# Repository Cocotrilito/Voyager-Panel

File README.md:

<div align="center">

# ⟡ VOYAGER PANEL ⟡

### An E-Ink travel dashboard

`ESP32-S3` · `296×128 E-Paper` · `Battery Powered` · `Wi-Fi` · `Low Power`

</div>

---

An E-Ink travel dashboard. with an ESP32-S3 Showing weather, hackclub countdowns, and travel info for hackactons. this dashboard has Low-Power consumption, Wi-Fi connected, battery-operated!!!!

---

## ⟡ The reason behind this project

This project started from the *dream* of always wanting to have a big countdown telling you the Narrow door for a better future is closing, yeah crazy right?, hahaha well actually this project started in the supermarket of my local city, I was shopping and noticed an E-Ink display, I thought *I have seen this before* and it was when I was searching my first project I saw something called E-Ink dashboard, and was cool but I thought Im too newbie for this, so I challenged myself to improve my PCB designer skills and I think I did a really cool project, im really proud of it tbh, well but in the end the actual big reason is to truly have a giant countdown telling you stasis is over in X days or telling you your youth days are over in X days I love presure >:D

---

## ⟡ Schematic Overview

<div align="center">

</div>

---

## ⟡ PCB — DIFFERENT VERSIONS

<div align="center">

</div>

<table>
<tr>
<td width="50%"></td>
<td width="50%"></td>
</tr>
<tr>
<td align="center"><b>Back copper</b></td>
<td align="center"><b>Front copper</b></td>
</tr>
</table>

---

## ⟡ RENDER!!

<div align="center">

</div>

<table>
<tr>
<td width="50%"></td>
<td width="50%"></td>
</tr>
<tr>
<td align="center"><b>Front</b></td>
<td align="center"><b>Back</b></td>
</tr>
</table>

---

## ⟡ Hardware at a glance

| | |
|---|---|
| **MCU** | ESP32-S3-MINI-1 — Wi-Fi, BLE, native USB |
| **Display** | Waveshare 2.9" e-Paper, 296×128, SSD1680 controller |
| **Sensor** | BMP280 over I2C — temperature, pressure, derived altitude |
| **Power** | 1000 mAh LiPo, TP4056 charger, MCP1700 LDO |
| **Protection** | TVS ESD array, Schottky reverse-current diode, 500 mA polyfuse |
| **Programming** | Native USB-C, no external UART bridge |

---

## ⟡ Firmware

Built with **PlatformIO** on the Arduino framework.

```
firmware/VoyagerPanelFirmware/
├── platformio.ini
└── src/
    ├── main.cpp
    └── images.h
```

Because the board uses the ESP32-S3's native USB and carries no USB-UART bridge,
`Serial` has to be routed to the USB CDC peripheral. Without these flags nothing
reaches the host:

```ini
build_flags =
    -D ARDUINO_USB_MODE=1
    -D ARDUINO_USB_CDC_ON_BOOT=1
```

The sensor and the display initialise **independently**, so a failure in one does not
take down the other. The dashboard degrades gracefully instead of hanging.

### Live telemetry

```
========== VOYAGER SENSOR ==========
  Temperature : 29.29 C
  Pressure    : 751.36 hPa
  Altitude    : 2452.2 m
====================================
```

---

## ⟡ Debugging log

The display refused to render, and tracking down why turned into the most interesting
part of this build — a full diagnosis of a hardware fault carried out **without a
multimeter**, using the microcontroller itself as the measuring instrument.

Short version: the SSD1680 was running on **phantom power**, leaking current through
its own ESD protection diodes. Enough to acknowledge a reset, not enough to execute a
single SPI command.

The full write-up, including the software continuity matrix used to prove it, lives in
**[DEBUGGING.md](DEBUGGING.md)**.

A second find along the way: the module sold as a BME280 is actually a **BMP280**. Its
chip ID register returns `0x58` instead of `0x60`, and it has no humidity channel. The
firmware reads that register and picks the right driver rather than trusting the label.

---

## ⟡ BOM

| Name | Purpose | Qty | Cost (USD) | Distributor |
|------|---------|-----|-----------|-------------|
| ESP32-S3-MINI-1 | Main microcontroller with WiFi and USB native | 1 | $8.50 | AliExpress |
| Waveshare 2.9inch e-Paper Module | Main e-ink display 296x128px | 1 | $17.00 | AliExpress |
| BME280 Breakout Module | Temperature/Humidity/Pressure sensor | 1 | $5.15 | AliExpress |
| LiPo Battery 1000mAh 3.7V | Portable power source | 1 | $5.00 | Local Ecuador |
| USB-C Receptacle 16P | Power input and native USB programming | 1 | $0.50 | JLCPCB |
| JST PH 2mm 2-Pin Connector | Battery connector | 1 | $0.10 | JLCPCB |
| Pin Header 1x08 2.54mm | E-ink display connector | 1 | $0.05 | Local |
| Pin Header 1x04 2.54mm | BME280 module connector | 1 | $0.05 | Local |
| TP4056-42-ESOP8 | LiPo battery charger IC | 1 | $0.15 | JLCPCB |
| MCP1700-3302 SOT-89 | 3.3V LDO regulator 0.2V dropout | 1 | $0.45 | JLCPCB |
| SP0503BAHTG SOT-363 | TVS ESD protection diode for USB | 1 | $0.20 | JLCPCB |
| SS14 SMA | Schottky diode reverse current protection | 1 | $0.05 | JLCPCB |
| Polyfuse 500mA 1206 | Resettable overcurrent fuse | 1 | $0.10 | JLCPCB |
| SW_SPST_TL3342 | Tactile buttons Reset/Boot/Next/Select | 4 | $0.05 | JLCPCB |
| LED 0805 Red | Battery charging indicator CHRG | 1 | $0.02 | JLCPCB |
| LED 0805 Blue | Standby indicator STDBY | 1 | $0.02 | JLCPCB |
| LED 0805 Green | System status indicator | 1 | $0.02 | JLCPCB |
| Resistor 1k 0805 | LED current limiting resistors | 3 | $0.03 | JLCPCB |
| Resistor 2.2k 0805 | TP4056 charge current set 550mA | 1 | $0.01 | JLCPCB |
| Resistor 4.7k 0805 | I2C SDA/SCL pull-up resistors | 2 | $0.02 | JLCPCB |
| Resistor 5.1k 0805 | USB-C CC1/CC2 pull-down resistors | 2 | $0.02 | JLCPCB |
| Resistor 10k 0805 | Pull-ups for EN/BOOT/UI buttons | 5 | $0.05 | JLCPCB |
| Resistor 27R 0805 | USB D+/D- series termination | 2 | $0.02 | JLCPCB |
| Capacitor 100nF 0805 | High frequency decoupling | 5 | $0.05 | JLCPCB |
| Capacitor 1uF 0805 | EN pin reset debounce | 1 | $0.02 | JLCPCB |
| Capacitor 10uF 0805 | Bulk decoupling capacitors | 5 | $0.15 | JLCPCB |
| Capacitor 22uF 0805 | ESP32 main power bulk decoupling | 1 | $0.05 | JLCPCB |
| PCB + SMT Assembly | 2-layer PCB with PCBA | 1 | $47.90 | JLCPCB |
| **TOTAL** | | | **$85.42** | |

---

## ⟡ Repository layout

```
├── cad/                          Fusion 360 enclosure + renders
├── docs/references/              Datasheets and reference material
├── firmware/
│   ├── VoyagerPanelFirmware/     PlatformIO project
│   └── diagnostics/              Hardware bring-up test sketches
├── images/                       Schematic, PCB, and build photos
├── projectFiles/
├── voyagerPanel/                 KiCad project
├── DEBUGGING.md
└── README.md
```

---

## ⟡ Final notes!

Thanks for reading! made possible with http://stasis.hackclub.com/

---

<div align="center">

## ⟡ me

*By cocotrilo*

**made with luv (THIS ONE was with a lot of love, EXCEPT FOR THE BOM PLEASE DONT USE EVER ALIEXPRESS) Nk but luv from EC <3**

</div>

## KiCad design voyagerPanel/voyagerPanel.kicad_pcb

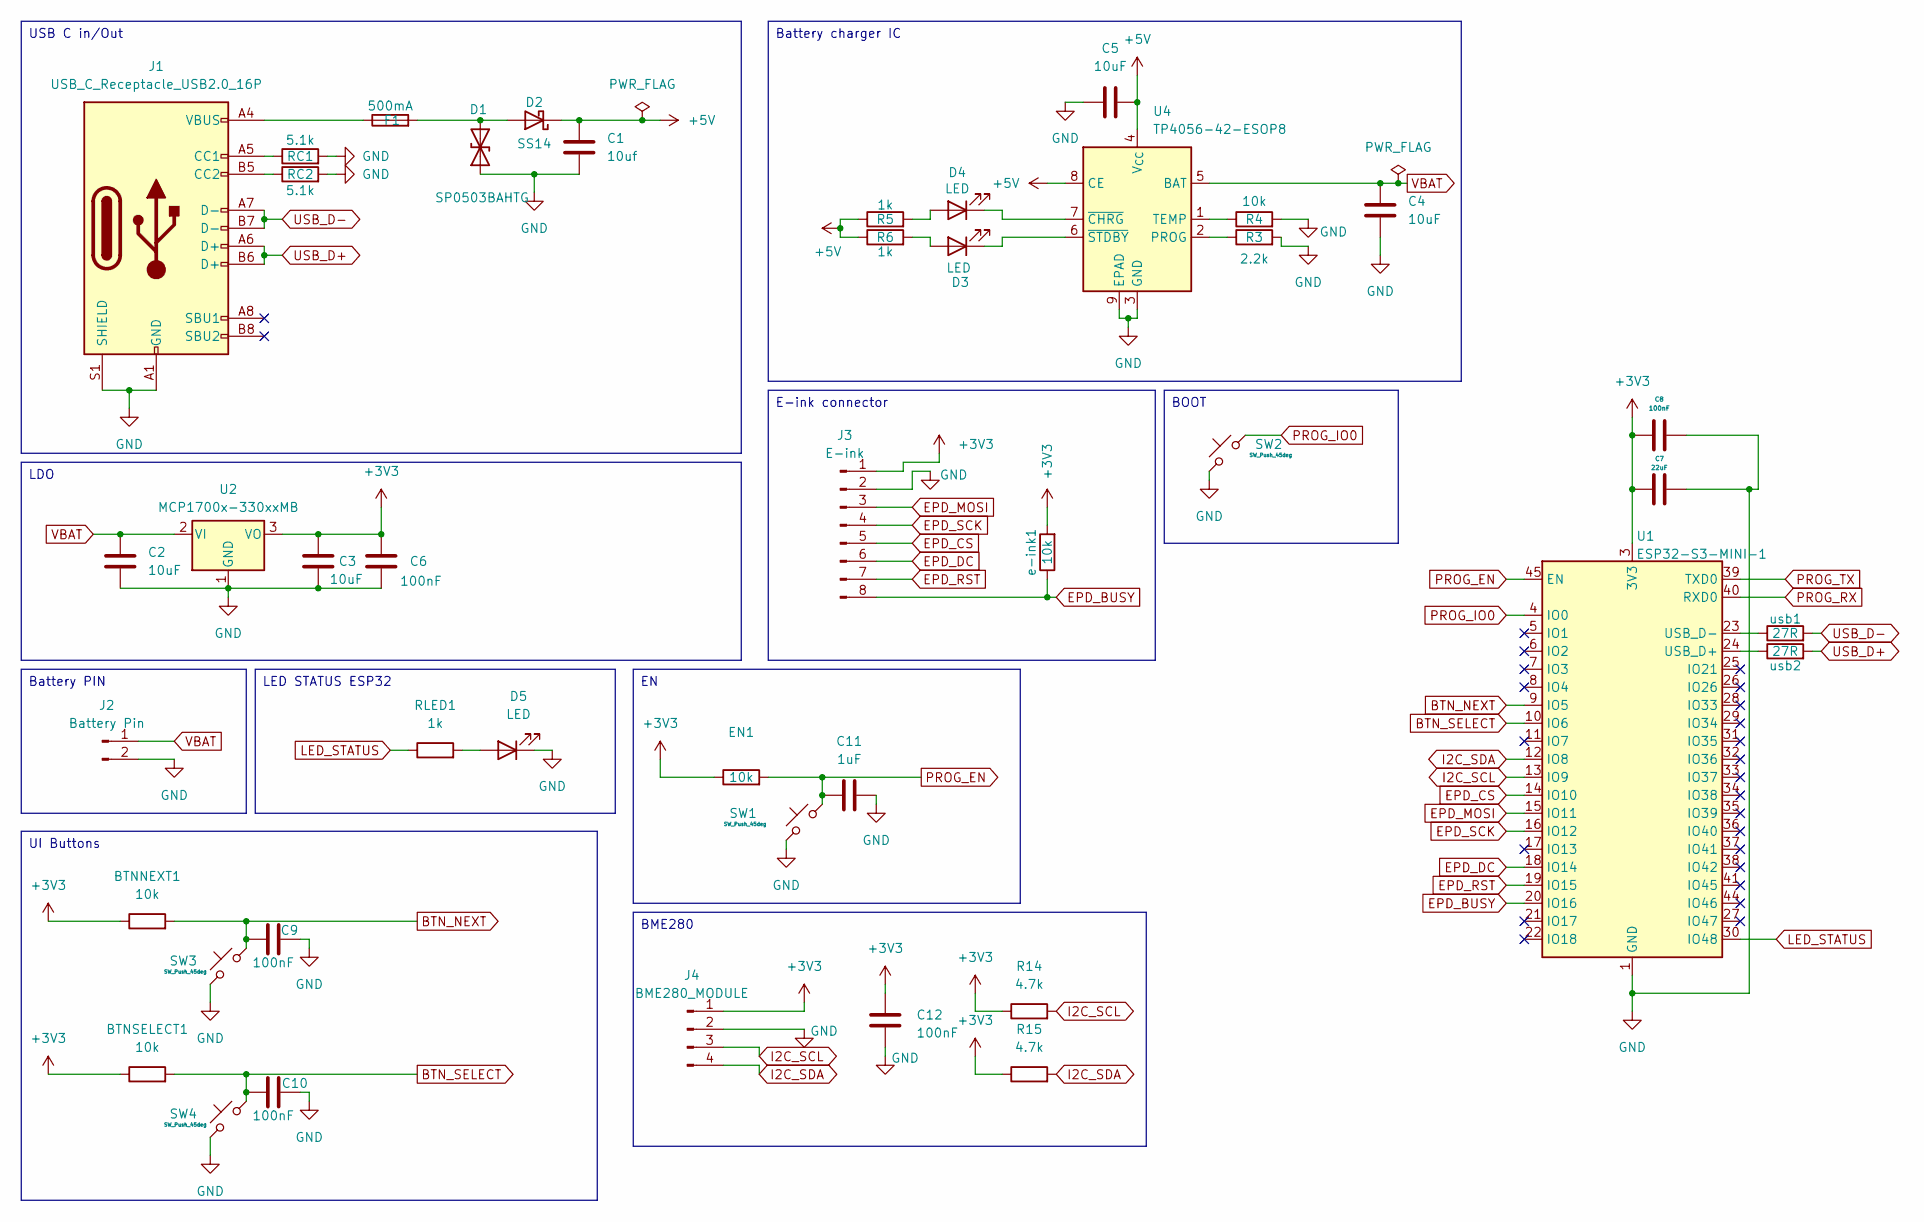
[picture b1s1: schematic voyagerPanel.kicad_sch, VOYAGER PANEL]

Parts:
BTNNEXT1: 10k; R_0805_2012Metric
BTNSELECT1: 10k; R_0805_2012Metric
C1: 10uf; C_0805_2012Metric
C2, C3, C4, C5: 10uF; C_0805_2012Metric
C6, C8, C9, C10, C12: 100nF; C_0805_2012Metric
C7: 22uF; C_0805_2012Metric
C11: 1uF; C_0805_2012Metric
D1: SP0503BAHTG; SOT-363_SC-70-6
D2: SS14; D_SMA
D3, D4, D5: LED; LED_0805_2012Metric
EN1: 10k; R_0805_2012Metric
F1: 500mA; Fuse_1206_3216Metric
J1: USB_C_Receptacle_USB2.0_16P; USB_C_Receptacle_HRO_TYPE-C-31-M-12
J2: Battery Pin; JST_PH_B2B-PH-K_1x02_P2.00mm_Vertical
J3: E-ink; PinHeader_1x08_P2.54mm_Vertical
J4: BME280_MODULE; PinHeader_1x04_P2.54mm_Vertical
R3: 2.2k; R_0805_2012Metric
R4: 10k; R_0805_2012Metric
R5, R6: 1k; R_0805_2012Metric
R14, R15: 4.7k; R_0805_2012Metric
RC1, RC2: 5.1k; R_0805_2012Metric
RLED1: 1k; R_0805_2012Metric
SW1, SW2, SW3, SW4: SW_Push_45deg; SW_SPST_TL3342
U1: ESP32-S3-MINI-1; ESP32-S2-MINI-1
U2: MCP1700x-330xxMB; SOT-89-3
U4: TP4056-42-ESOP8; SOIC-8-1EP_3.9x4.9mm_P1.27mm_EP2.41x3.3mm_ThermalVias
e-ink1: 10k; R_0805_2012Metric
usb1, usb2: 27R; R_0805_2012Metric

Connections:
+3V3: BTNNEXT1.1, BTNSELECT1.1, C3.1, C6.1, C7.1, C8.1, C12.1, EN1.1, J3.1, J4.1, R14.1, R15.1, U1.3 (3V3), U2.3 (VO), e-ink1.2; also elsewhere on the board
+5V: C1.1, C5.2, D2.1 (K), R5.1, R6.1, U4.4 (V_{CC}), U4.8 (CE)
BTN_NEXT: BTNNEXT1.2, C9.1, SW3.2, U1.9 (IO5); also elsewhere on the board
BTN_SELECT: BTNSELECT1.2, C10.1, SW4.2, U1.10 (IO6); also elsewhere on the board
EPD_BUSY: J3.8, U1.20 (IO16), e-ink1.1
EPD_CS: J3.5, U1.14 (IO10)
EPD_DC: J3.6, U1.18 (IO14)
EPD_MOSI: J3.3, U1.15 (IO11)
EPD_RST: J3.7, U1.19 (IO15)
EPD_SCK: J3.4, U1.16 (IO12)
GND: C1.2, C2.2, C3.2, C4.2, C5.1, C6.2, C7.2, C8.2, C9.2, C10.2, C11.1, C12.2, D1.1 (A1), D5.1 (K), J1.A1 (GND), J1.A12 (GND), J1.B1 (GND), J1.B12 (GND), J1.S1 (SHIELD), J2.2, J3.2, J4.2, R3.2, R4.2, RC1.2, RC2.2, SW1.1, SW2.1, SW3.1, SW4.1, U1.1 (GND), U1.2 (GND), U1.42 (GND), U1.43 (GND), U1.46 (GND), U1.47 (GND), U1.48 (GND), U1.49 (GND), U1.50 (GND), U1.51 (GND), U1.52 (GND), U1.53 (GND), U1.54 (GND), U1.55 (GND), U1.56 (GND), U1.57 (GND), U1.58 (GND), U1.59 (GND), U1.60 (GND), U1.61 (GND), U1.62 (GND), U1.63 (GND), U1.64 (GND), U1.65 (GND), U2.1 (GND), U4.3 (GND), U4.9 (EPAD)
I2C_SCL: J4.3, R14.2, U1.13 (IO9)
I2C_SDA: J4.4, R15.2, U1.12 (IO8)
LED_STATUS: RLED1.1, U1.30 (IO48)
unnamed: D1.2 (A2), D2.2 (A), F1.2
unnamed: D3.2 (A), R6.2
unnamed: D3.1 (K), U4.6 (~STDBY)
unnamed: D4.2 (A), R5.2
unnamed: D4.1 (K), U4.7 (~CHRG)
unnamed: D5.2 (A), RLED1.2
unnamed: F1.1, J1.A4 (VBUS), J1.A9 (VBUS), J1.B4 (VBUS), J1.B9 (VBUS)
unnamed: J1.A5 (CC1), RC1.1
unnamed: J1.B5 (CC2), RC2.1
unnamed: U1.24 (USB_D+), usb2.1
unnamed: U1.23 (USB_D-), usb1.1
unnamed: R3.1, U4.2 (PROG)
unnamed: R4.1, U4.1 (TEMP)
PROG_EN: C11.2, EN1.2, SW1.2, U1.45 (EN)
PROG_IO0: SW2.2, U1.4 (IO0)
PROG_RX: U1.40 (RXD0)
PROG_TX: U1.39 (TXD0)
USB_D+: J1.A6 (D+), J1.B6 (D+), usb2.2
USB_D-: J1.A7 (D-), J1.B7 (D-), usb1.2
VBAT: C2.1, C4.1, J2.1, U2.2 (VI), U4.5 (BAT)

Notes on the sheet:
Battery PIN
LDO
E-ink connector
UI Buttons
Battery charger IC
BOOT
USB C in/Out
BME280
LED STATUS ESP32

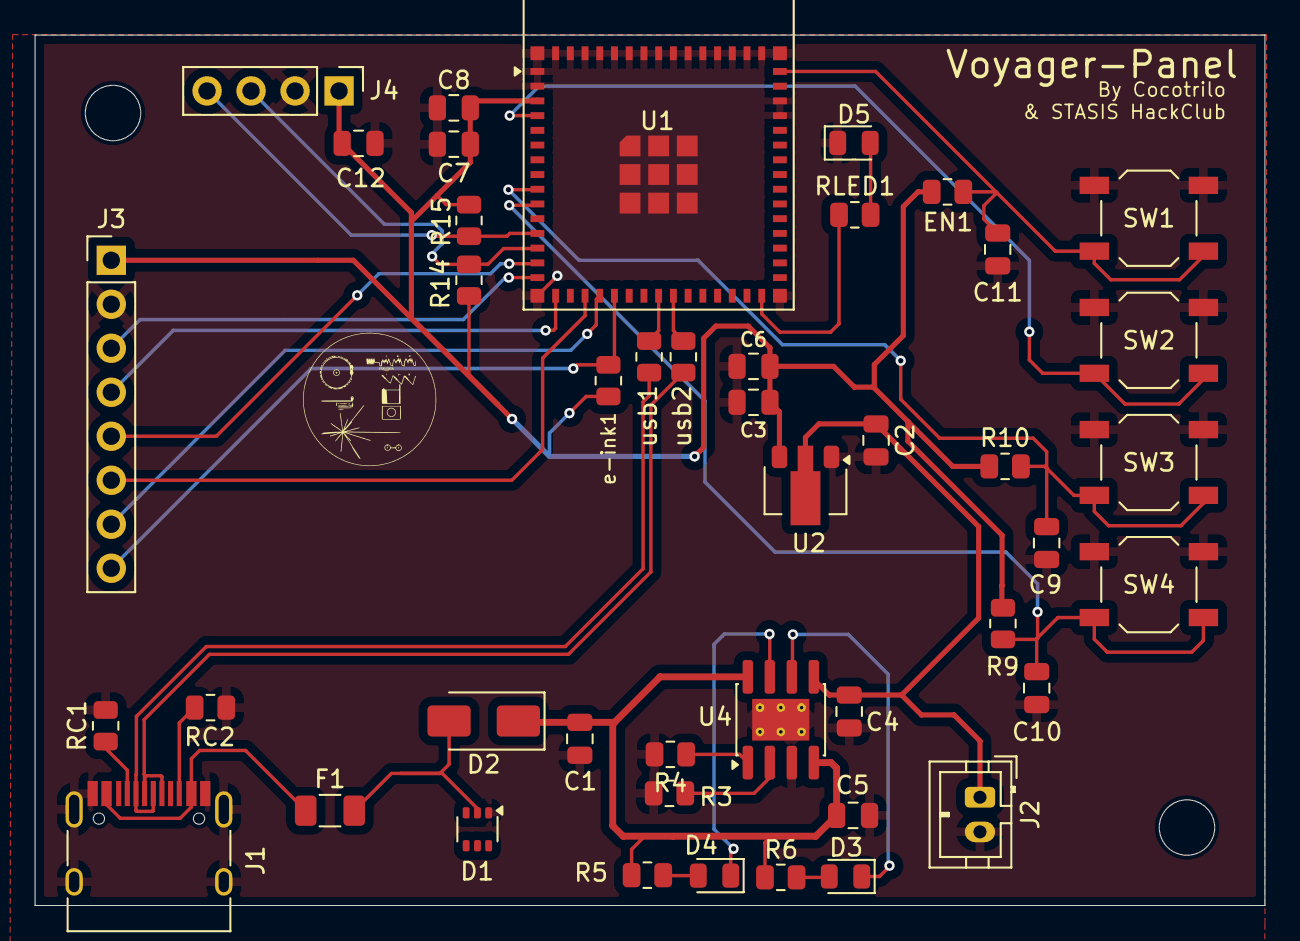
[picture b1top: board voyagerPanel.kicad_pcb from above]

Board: 2 copper layers, 71.0 x 50.3 mm, 44 parts (0 on the bottom side), 32 nets.

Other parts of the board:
R9, R10: 10k; R_0805_2012Metric

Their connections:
+3V3: R9.1, R10.1; also elsewhere on the board
BTN_NEXT: R10.2; also elsewhere on the board
BTN_SELECT: R9.2; also elsewhere on the board

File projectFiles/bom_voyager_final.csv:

Name,Purpose,Quantity,Unit Cost (USD),Total Cost (USD),Distributor,Link
ESP32-S3-MINI-1,Main microcontroller with WiFi and USB native,1,$8.50,$8.50,AliExpress,https://www.aliexpress.com/item/ESP32-S3-MINI-1.html
Waveshare 2.9inch e-Paper Module,Main e-ink display 296x128px,1,$17.00,$17.00,AliExpress,https://www.waveshare.com/2.9inch-e-paper-module.htm
BME280 Breakout Module,Temperature/Humidity/Pressure sensor,1,$5.15,$5.15,AliExpress,https://www.aliexpress.us/item/3256805961500122.html
LiPo Battery 1000mAh 3.7V,Portable power source - bought locally,1,$5.00,$5.00,Local Ecuador,N/A
USB-C Receptacle 16P,Power input and native USB programming,1,$0.50,$0.50,JLCPCB/LCSC,https://www.lcsc.com/product-detail/C165948.html
JST PH 2mm 2-Pin Connector,Battery connector,1,$0.10,$0.10,JLCPCB/LCSC,https://www.lcsc.com/product-detail/C295747.html
Pin Header 1x08 2.54mm,E-ink display connector,1,$0.05,$0.05,Local/AliExpress,N/A
Pin Header 1x04 2.54mm,BME280 module connector,1,$0.05,$0.05,Local/AliExpress,N/A
TP4056-42-ESOP8,LiPo battery charger IC up to 550mA,1,$0.15,$0.15,JLCPCB/LCSC,https://www.lcsc.com/product-detail/C16581.html
MCP1700-3302 SOT-89,3.3V LDO regulator 0.2V dropout,1,$0.45,$0.45,JLCPCB/LCSC,https://www.lcsc.com/product-detail/C5446.html
SP0503BAHTG SOT-363,TVS ESD protection diode for USB,1,$0.20,$0.20,JLCPCB/LCSC,https://www.lcsc.com/product-detail/C558442.html
SS14 SMA,Schottky diode reverse current protection,1,$0.05,$0.05,JLCPCB/LCSC,https://www.lcsc.com/product-detail/C2480.html
Polyfuse 500mA 1206,Resettable overcurrent fuse,1,$0.10,$0.10,JLCPCB/LCSC,https://www.lcsc.com/product-detail/C69688.html
SW_SPST_TL3342 x4,Tactile buttons - Reset/Boot/Next/Select,4,$0.05,$0.20,JLCPCB/LCSC,https://www.lcsc.com/product-detail/C2886894.html
LED 0805 Red,Battery charging indicator (CHRG),1,$0.02,$0.02,JLCPCB/LCSC,https://www.lcsc.com/product-detail/C84256.html
LED 0805 Blue,Standby indicator (STDBY),1,$0.02,$0.02,JLCPCB/LCSC,https://www.lcsc.com/product-detail/C72041.html
LED 0805 Green,System status indicator,1,$0.02,$0.02,JLCPCB/LCSC,https://www.lcsc.com/product-detail/C72043.html
Resistor 1k 0805 x3,LED current limiting resistors,3,$0.01,$0.03,JLCPCB/LCSC,https://www.lcsc.com/product-detail/C17513.html
Resistor 2.2k 0805,TP4056 charge current set (~550mA),1,$0.01,$0.01,JLCPCB/LCSC,https://www.lcsc.com/product-detail/C17520.html
Resistor 4.7k 0805 x2,I2C SDA/SCL pull-up resistors,2,$0.01,$0.02,JLCPCB/LCSC,https://www.lcsc.com/product-detail/C17673.html
Resistor 5.1k 0805 x2,USB-C CC1/CC2 pull-down resistors,2,$0.01,$0.02,JLCPCB/LCSC,https://www.lcsc.com/product-detail/C23186.html
Resistor 10k 0805 x5,Pull-ups for EN/BOOT/UI buttons,5,$0.01,$0.05,JLCPCB/LCSC,https://www.lcsc.com/product-detail/C17414.html
Resistor 27R 0805 x2,USB D+/D- series termination resistors,2,$0.01,$0.02,JLCPCB/LCSC,https://www.lcsc.com/product-detail/C17719.html
Capacitor 100nF 0805 x5,High frequency decoupling capacitors,5,$0.01,$0.05,JLCPCB/LCSC,https://www.lcsc.com/product-detail/C49678.html
Capacitor 1uF 0805,EN pin reset debounce capacitor,1,$0.02,$0.02,JLCPCB/LCSC,https://www.lcsc.com/product-detail/C28323.html
Capacitor 10uF 0805 x5,Bulk decoupling capacitors,5,$0.03,$0.15,JLCPCB/LCSC,https://www.lcsc.com/product-detail/C15850.html
Capacitor 22uF 0805,ESP32 main power bulk decoupling,1,$0.05,$0.05,JLCPCB/LCSC,https://www.lcsc.com/product-detail/C45783.html
PCB Manufacturing x5,Custom 2-layer PCB with SMT assembly,1,$47.90,$47.90,JLCPCB,https://jlcpcb.com
TOTAL,,,,~$85.42,,

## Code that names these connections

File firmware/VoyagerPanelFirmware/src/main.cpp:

#include <Arduino.h>
#include <Wire.h>
#include <SPI.h>
#include <Adafruit_BMP280.h>
#include <GxEPD2_BW.h>
#include <Fonts/FreeMonoBold9pt7b.h>
#include "images.h"

// pins for more info look into the schmeatic in the github
static const int PIN_LED    = 48;
static const int PIN_SDA    = 8;
static const int PIN_SCL    = 9;
static const int PIN_EPD_CS   = 10;
static const int PIN_EPD_MOSI = 11;
static const int PIN_EPD_SCK  = 12;
static const int PIN_EPD_DC   = 14;
static const int PIN_EPD_RST  = 15;
static const int PIN_EPD_BUSY = 16;
static const uint8_t SENSOR_ADDR = 0x76;
static const float   SEA_LEVEL_HPA = 1013.25f; 

Adafruit_BMP280 sensor;
GxEPD2_BW<GxEPD2_290_T94_V2, GxEPD2_290_T94_V2::HEIGHT>
    display(GxEPD2_290_T94_V2(PIN_EPD_CS, PIN_EPD_DC, PIN_EPD_RST, PIN_EPD_BUSY));

struct Telemetry {
  float temperature;   // C
  float pressure;      // hPa
  float altitude;      // m
  bool  valid;
};

static bool sensorReady  = false;
static bool displayReady = false;
RTC_DATA_ATTR int currentPage = 0;


static uint8_t readChipId() {
  Wire.beginTransmission(SENSOR_ADDR);
  Wire.write(0xD0);
  if (Wire.endTransmission() != 0) return 0xFF;
  Wire.requestFrom(SENSOR_ADDR, (uint8_t)1);
  return Wire.available() ? Wire.read() : 0xFF;
}

static bool initSensor() {
  Wire.begin(PIN_SDA, PIN_SCL);
  delay(100);

  uint8_t id = readChipId();
  Serial.printf("Sensor chip ID: 0x%02X\n", id);

  if (!sensor.begin(SENSOR_ADDR)) {
    Serial.println("Sensor init failed.");
    return false;
  }

  sensor.setSampling(Adafruit_BMP280::MODE_NORMAL,
                     Adafruit_BMP280::SAMPLING_X2,
                     Adafruit_BMP280::SAMPLING_X16,
                     Adafruit_BMP280::FILTER_X16,
                     Adafruit_BMP280::STANDBY_MS_500);

  Serial.println("Sensor ready.");
  return true;
}

static Telemetry readTelemetry() {
  Telemetry t = {0, 0, 0, false};
  if (!sensorReady) return t;

  t.temperature = sensor.readTemperature();
  t.pressure    = sensor.readPressure() / 100.0f;
  t.altitude    = sensor.readAltitude(SEA_LEVEL_HPA);
  t.valid       = !isnan(t.temperature);
  return t;
}

static bool initDisplay() {
  display.init(0, true, 10, false);
  SPI.end();
  SPI.begin(PIN_EPD_SCK, -1, PIN_EPD_MOSI, PIN_EPD_CS);
  display.setRotation(1);
  display.setFont(&FreeMonoBold9pt7b);
  display.setTextColor(GxEPD_BLACK);
  if (digitalRead(PIN_EPD_BUSY) == HIGH) {
    Serial.println("Display busy line stuck high.");
    return false;
  }

  Serial.println("Display ready.");
  return true;
}

static void renderDashboard(const Telemetry &t) {
  if (!displayReady) return;

  display.setFullWindow();
  display.firstPage();
  do {
    display.fillScreen(GxEPD_WHITE);
    display.drawInvertedBitmap(0, 0, world_map_bitmap, 296, 128, GxEPD_BLACK);

    
    display.fillRect(0, 0, 160, 22, GxEPD_WHITE);
    display.setCursor(4, 16);
    display.print("VOYAGER / ORBIT");

    display.fillRect(0, 106, 296, 22, GxEPD_WHITE);
    display.setCursor(4, 122);
    if (t.valid) {
      display.printf("%.1fC  %.0fhPa  %.0fm", t.temperature, t.pressure, t.altitude);
    } else {
      display.print("SENSOR OFFLINE");
    }
  } while (display.nextPage());
}

//inicio de todo

void setup() {
  pinMode(PIN_LED, OUTPUT);
  digitalWrite(PIN_LED, LOW);

  Serial.begin(115200);
  uint32_t start = millis();
  while (!Serial && millis() - start < 3000) delay(10);

  Serial.println("\nVoyager Panel booting...");

  sensorReady  = initSensor();
  displayReady = initDisplay();

  renderDashboard(readTelemetry());
}

void loop() {
  static uint32_t lastRefresh = 0;
  const uint32_t REFRESH_INTERVAL = 60000;   

  Telemetry t = readTelemetry();

  if (t.valid) {
    Serial.printf("T=%.2fC  P=%.2fhPa  Alt=%.1fm\n",
                  t.temperature, t.pressure, t.altitude);
  }

  if (displayReady && millis() - lastRefresh > REFRESH_INTERVAL) {
    renderDashboard(t);
    lastRefresh = millis();
  }

  digitalWrite(PIN_LED, HIGH);
  delay(100);
  digitalWrite(PIN_LED, LOW);
  delay(1900);
}

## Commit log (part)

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2026-04-18 start
2026-04-19 Day One schematic power esp32
2026-04-19 Finished schematic creating pcb
2026-04-20 PCB almost finished end of day 2
2026-04-21 finished PCB
2026-04-23 Firmware finalized!
2026-04-24 final push
2026-04-24 Update README with project details and visuals
    Expanded project description and added sections for schematic, PCB versions, render, BOM, and final notes.
2026-04-24 Update README.md
    BOM i forgot
2026-04-28 Fix image link formatting in README.md
2026-04-28 Update README with additional PCB images
    Added images for back and front BCU/FCU to README.
2026-04-29 Remade CAD models
